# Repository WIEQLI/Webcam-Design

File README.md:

# Webcam-Design
A team project at Northwestern University

This project involves a printed circuit design using PCB CAD software, surface mount soldering, MCU programming, CAD design for 3D printing, and web design.

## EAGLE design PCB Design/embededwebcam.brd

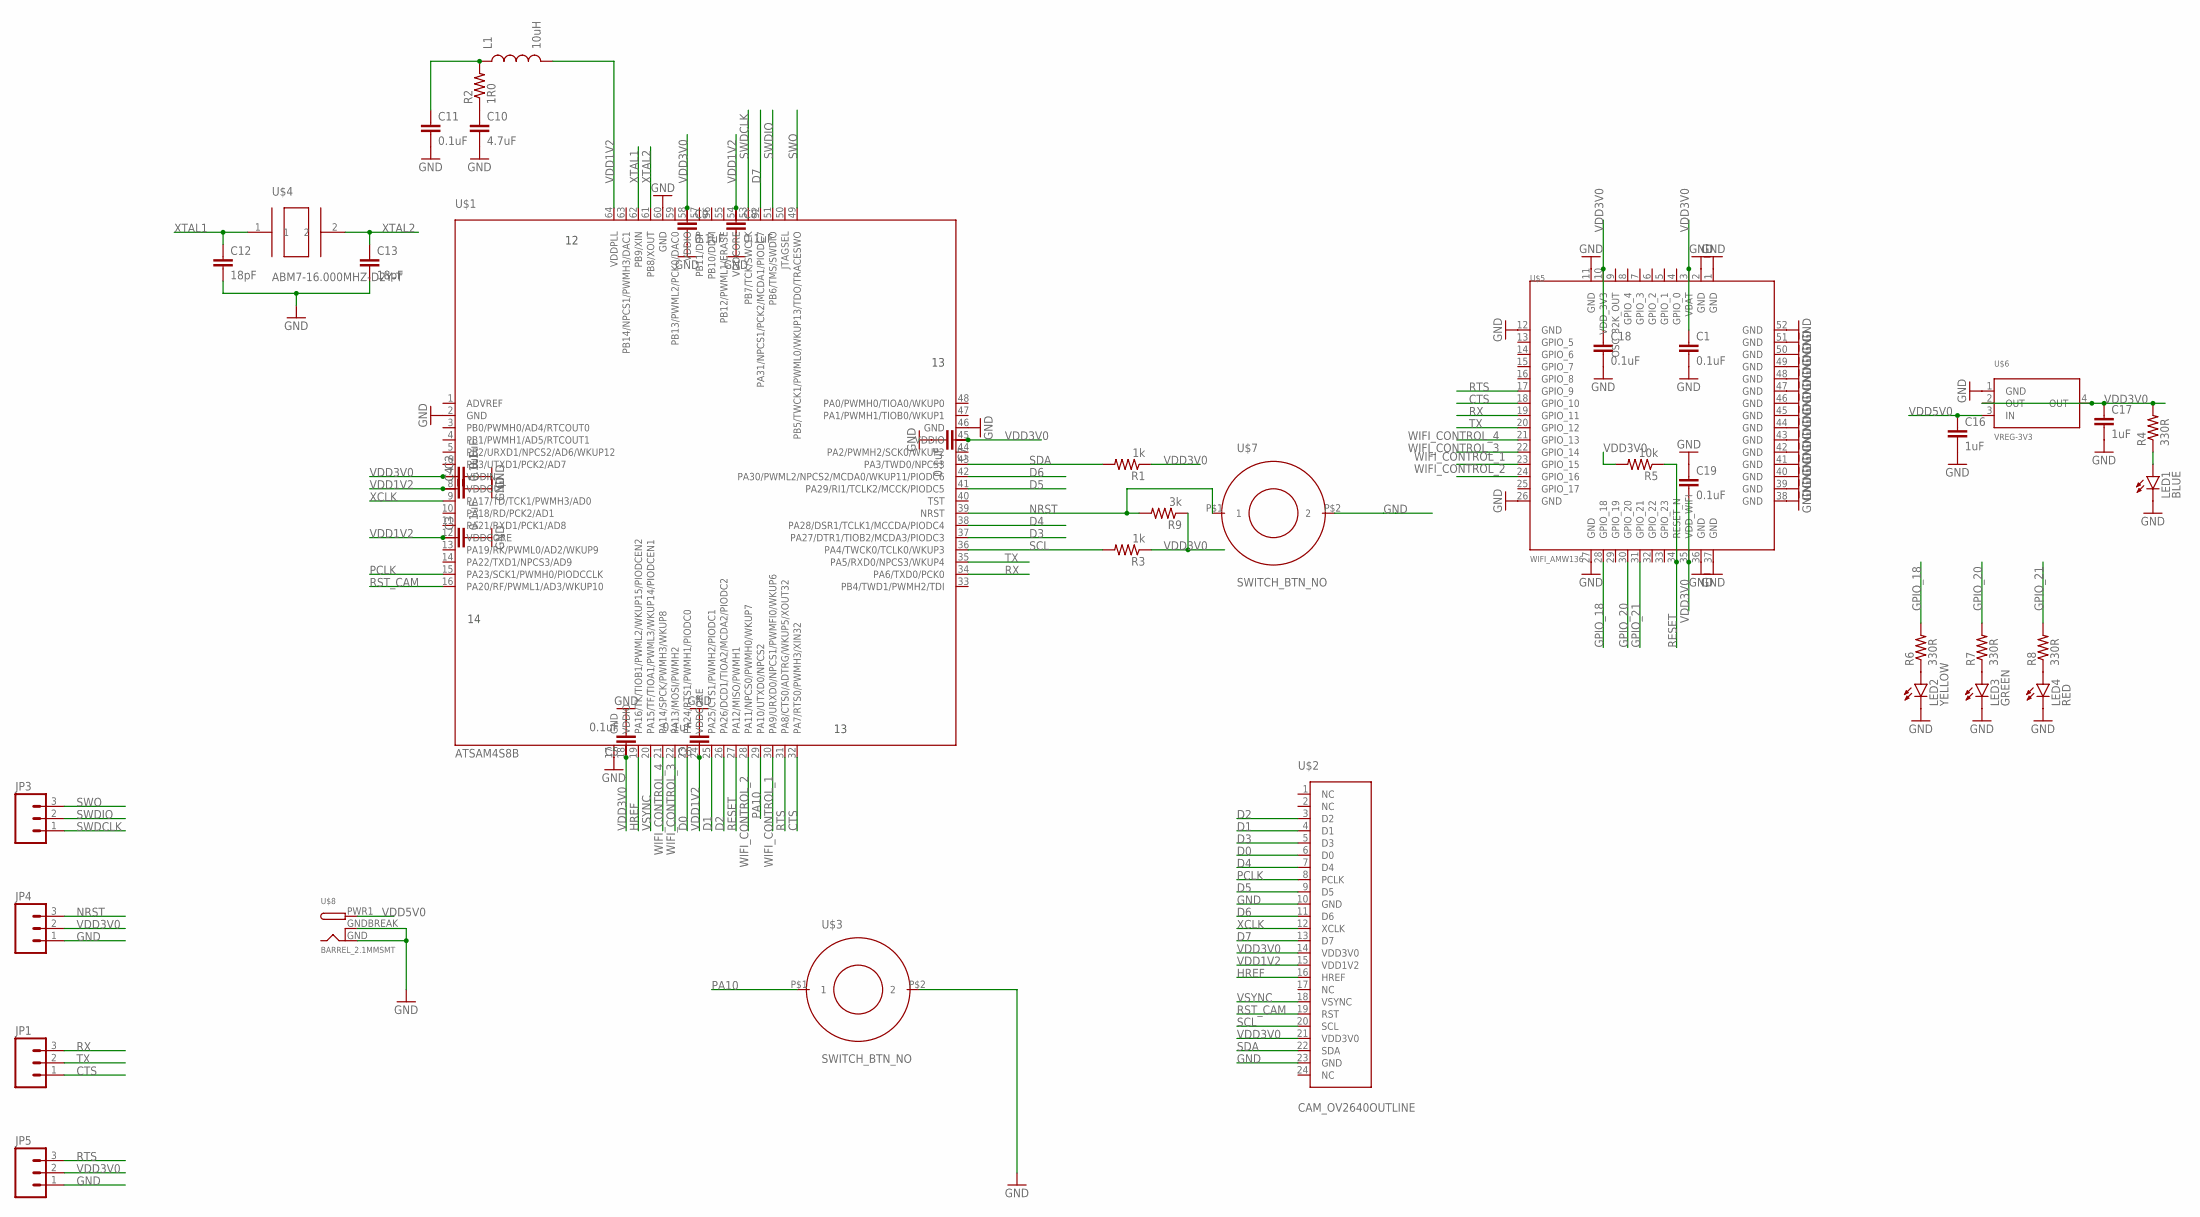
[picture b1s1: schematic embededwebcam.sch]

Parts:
C1, C2, C3, C4, C5, C6, C7, C8, C9, C11, C18, C19: 0.1uF; 0805
C10: 4.7uF; 0805
C12, C13: 18pF; 0805
C16, C17: 1uF; 0805
JP1, JP3, JP4, JP5: M03PTH; 1X03
L1: 10uH; 0805
LED1: BLUE; LED-0603
LED2: YELLOW; LED-0603
LED3: GREEN; LED-0603
LED4: RED; LED-0603
R1, R3: 1k; 0805
R2: 1R0; 0805
R4, R6, R7, R8: 330R; 0805
R5: 10k; 0805
R9: 3k; 0805
U$1: ATSAM4S8B; QFP50P1200X1200X160-64N
U$2: CAM_OV2640OUTLINE; CAM_CONN
U$3, U$7: SWITCH_BTN_NO; BTN_2
U$4: ABM7-16.000MHZ-D2Y-T
U$5: WIFI_AMW136; AMW136
U$6: VREG-3V3; R-PDSO-G4_TI
U$8: BARREL_2.1MMSMT; DCJACK_2MM_SMT

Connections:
CTS: JP1.1, U$1.32 (PA7/RTS0/PWMH3/XIN32), U$5.18 (GPIO_10)
D0: U$1.23 (PA24/RTS1/PWMH1/PIODC0), U$2.6 (D0)
D1: U$1.25 (PA25/CTS1/PWMH2/PIODC1), U$2.4 (D1)
D2: U$1.26 (PA26/DCD1/TIOA2/MCDA2/PIODC2), U$2.3 (D2)
D3: U$1.37 (PA27/DTR1/TIOB2/MCDA3/PIODC3), U$2.5 (D3)
D4: U$1.38 (PA28/DSR1/TCLK1/MCCDA/PIODC4), U$2.7 (D4)
D5: U$1.41 (PA29/RI1/TCLK2/MCCK/PIODC5), U$2.9 (D5)
D6: U$1.42 (PA30/PWML2/NPCS2/MCDA0/WKUP11/PIODC6), U$2.11 (D6)
D7: U$1.52 (PA31/NPCS1/PCK2/MCDA1/PIODC7), U$2.13 (D7)
GND: C1.2, C2.2, C3.2, C4.2, C5.2, C6.2, C7.2, C8.2, C9.2, C10.2, C11.2, C12.2, C13.2, C16.2, C17.2, C18.2, C19.1, JP4.1, JP5.1, LED1.C, LED2.C, LED3.C, LED4.C, U$1.2 (GND), U$1.17 (GND), U$1.46 (GND), U$1.60 (GND), U$2.10 (GND), U$2.23 (GND), U$3.P$2 (2), U$5.1 (GND), U$5.2 (GND), U$5.11 (GND), U$5.12 (GND), U$5.26 (GND), U$5.27 (GND), U$5.36 (GND), U$5.37 (GND), U$5.38 (GND), U$5.39 (GND), U$5.40 (GND), U$5.41 (GND), U$5.42 (GND), U$5.43 (GND), U$5.44 (GND), U$5.45 (GND), U$5.46 (GND), U$5.47 (GND), U$5.48 (GND), U$5.49 (GND), U$5.50 (GND), U$5.51 (GND), U$5.52 (GND), U$6.1 (GND), U$7.P$2 (2), U$8.GND, U$8.GNDBREAK
GPIO_18: R6.2, U$5.28 (GPIO_18)
GPIO_20: R7.2, U$5.30 (GPIO_20)
GPIO_21: R8.2, U$5.31 (GPIO_21)
HREF: U$1.19 (PA16/TK/TIOB1/PWML2/WKUP15/PIODCEN2), U$2.16 (HREF)
unnamed: C11.1, L1.1, R2.2
unnamed: C10.1, R2.1
unnamed: LED1.A, R4.1
unnamed: LED2.A, R6.1
unnamed: LED3.A, R7.1
unnamed: LED4.A, R8.1
NRST: JP4.3, R9.2, U$1.39 (NRST), U$7.P$1 (1)
PA10: U$1.29 (PA10/UTXD0/NPCS2), U$3.P$1 (1)
PCLK: U$1.15 (PA23/SCK1/PWMH0/PIODCCLK), U$2.8 (PCLK)
RESET: R5.1, U$1.27 (PA12/MISO/PWMH1), U$5.34 (RESET_N)
RST_CAM: U$1.16 (PA20/RF/PWML1/AD3/WKUP10), U$2.19 (RST)
RTS: JP5.3, U$1.31 (PA8/CTS0/ADTRG/WKUP5/XOUT32), U$5.17 (GPIO_9)
RX: JP1.3, U$1.34 (PA6/TXD0/PCK0), U$5.19 (GPIO_11)
SCL: R3.2, U$1.36 (PA4/TWCK0/TCLK0/WKUP3), U$2.20 (SCL)
SDA: R1.2, U$1.43 (PA3/TWD0/NPCS3), U$2.22 (SDA)
SWDCLK: JP3.1, U$1.53 (PB7/TCK/SWCLK)
SWDIO: JP3.2, U$1.51 (PB6/TMS/SWDIO)
SWO: JP3.3, U$1.49 (PB5/TWCK1/PWML0/WKUP13/TDO/TRACESWO)
TX: JP1.2, U$1.35 (PA5/RXD0/NPCS3/WKUP4), U$5.20 (GPIO_12)
VDD1V2: C3.1, C4.1, C6.1, C8.1, L1.2, U$1.8 (VDDOUT), U$1.12 (VDDCORE), U$1.24 (VDDCORE), U$1.54 (VDDCORE), U$1.64 (VDDPLL), U$2.15 (VDD1V2)
VDD3V0: C1.1, C2.1, C5.1, C7.1, C9.1, C17.1, C18.1, C19.2, JP4.2, JP5.2, R1.1, R3.1, R4.2, R5.2, R9.1, U$1.7 (VDDIN), U$1.18 (VDDIO), U$1.45 (VDDIO), U$1.58 (VDDIO), U$2.14 (VDD3V0), U$2.21 (VDD3V0), U$5.3 (VBAT), U$5.10 (VDD_3V3), U$5.35 (VDD_WIFI), U$6.2 (OUT), U$6.4 (OUT)
VDD5V0: C16.1, U$6.3 (IN), U$8.PWR1 (PWR)
VSYNC: U$1.20 (PA15/TF/TIOA1/PWML3/WKUP14/PIODCEN1), U$2.18 (VSYNC)
WIFI_CONTROL_1: U$1.30 (PA9/URXD0/NPCS1/PWMFI0/WKUP6), U$5.24 (GPIO_16)
WIFI_CONTROL_2: U$1.28 (PA11/NPCS0/PWMH0/WKUP7), U$5.23 (GPIO_15)
WIFI_CONTROL_3: U$1.22 (PA13/MOSI/PWMH2), U$5.22 (GPIO_14)
WIFI_CONTROL_4: U$1.21 (PA14/SPCK/PWMH3/WKUP8), U$5.21 (GPIO_13)
XCLK: U$1.9 (PA17/TD/TCK1/PWMH3/AD0), U$2.12 (XCLK)
XTAL1: C12.1, U$1.62 (PB9/XIN), U$4.1
XTAL2: C13.1, U$1.61 (PB8/XOUT), U$4.2

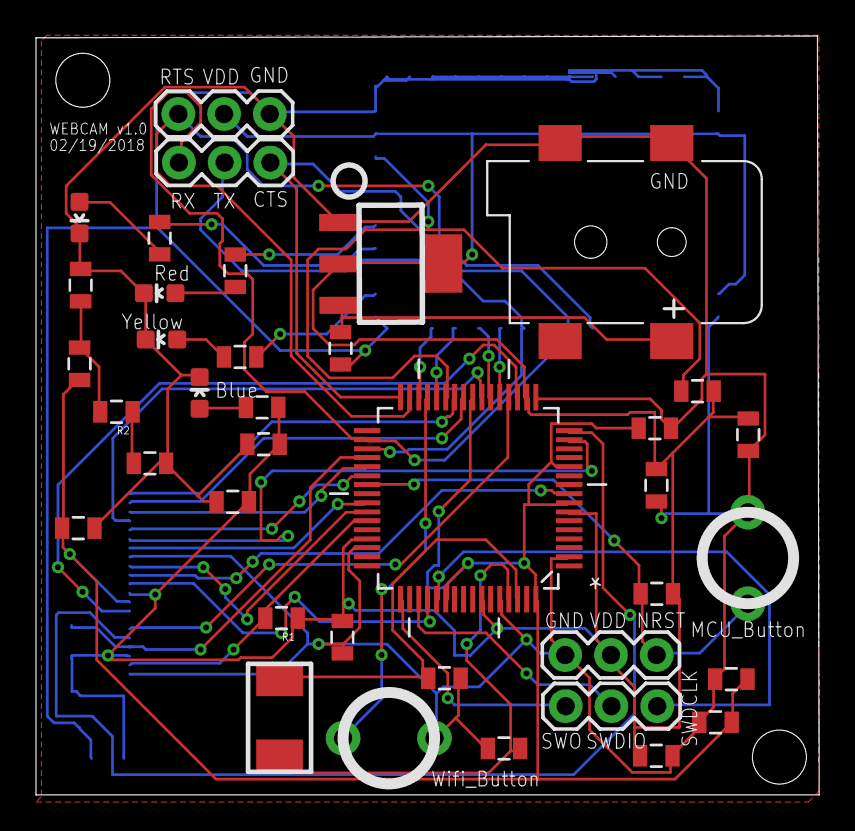
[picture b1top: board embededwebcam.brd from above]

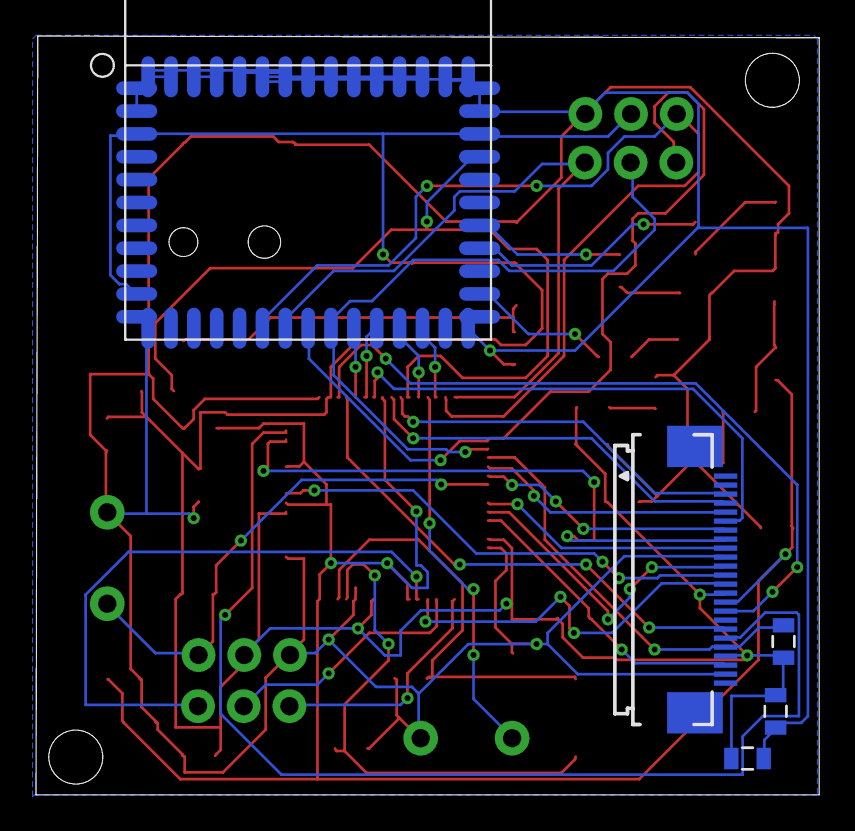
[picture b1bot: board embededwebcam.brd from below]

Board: 2 copper layers, 43.5 x 42.2 mm, 43 parts (5 on the bottom side), 44 nets.
